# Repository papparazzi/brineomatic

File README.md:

# Brineomatic Rev D-12V: a lower-cost 12 V remix of Brineomatic Rev-C1

This fork of [hoeken/brineomatic](https://github.com/hoeken/brineomatic) holds **Rev D-12V**, a remix of the Brineomatic **Rev-C1** watermaker controller for boats with a **12 V** supply. It aims to do everything Rev-C1 does at 12 V and to cost much less when JLCPCB assembles it. Brineomatic itself, its firmware and its documentation are hoeken's work: see [brineomatic.com](https://brineomatic.com).

> [!WARNING]
> **Status on 14 Nov 2026: design proposal. No board has been built or bench-tested.**
>
> This is not upstream's Rev D: upstream is designing its own 24 V Rev D on `main`.
>
> The latest design is on branch [`rev-d-12v-c57-100uf`][branch] (step 27). Read [Before you order](#before-you-order) first.

![Rev D-12V, top side (KiCad render, unchanged since step 26)][render]

## Contents

- [At a glance](#at-a-glance)
- [Why Rev-C1 is expensive to assemble](#why-rev-c1-is-expensive-to-assemble)
- [Cost comparison](#cost-comparison)
- [Every change, and why](#every-change-and-why)
- [Independent review](#independent-review)
- [Before you order](#before-you-order)
- [Branches and documents](#branches-and-documents)
- [Credits and license](#credits-and-license)

## At a glance

| | Rev-C1 (hoeken) | Rev D-12V (this fork) |
|---|---|---|
| Supply | 12-30 V DC | **12 V only** (9-15 V) |
| Controller | ESP32-S3-WROOM-1 module soldered on, USB-C on the board | ESP32-S3-DevKitC-1-N16R8 v1.1 dev board in two sockets, USB on the dev board |
| Input protection | TPS26630 eFuse with an N-channel reverse-polarity MOSFET | two P-channel reverse-polarity MOSFETs, then a TPS16630 eFuse (step 25) |
| Connectors | JST-PH, a 5.08 mm terminal, two 2x3 pin headers | one family: 3.5 mm pluggable screw terminals |
| Board | 106 x 63.5 mm, 4 layers | 160 x 90 mm, 4 layers |
| JLCPCB assembly | Standard PCBA (three parts are "Standard only") | Economic PCBA, top side only |
| BOM lines | 80 | 59 |
| Line fees | US$1.38 on each of 80 lines: US$110.05 | US$3.09 on each of 15 charged Extended lines: US$46.35 |
| 5 assembled boards | about US$376, US$75 each | about US$223 with the dev boards, US$45 each |
| Firmware | Rev C firmware | the same GPIO numbers, so the Rev C firmware should run unchanged (not tested) |
| Field record | 433 running hours reported by its author | none: untested |

The cost comes down in four moves:

1. **A plug-in ESP32 dev board** instead of the soldered module, USB-C and their support parts. This removes two "Standard only" parts and 8 charged lines.
2. **12 V only.** 16 V TVS diodes and 30 V MOSFETs are available as parts that JLCPCB loads free.
3. **Fee-free parts everywhere else.** 15 charged Extended lines are left. Rev-C1's BOM had 42 in an Economic trial quote.
4. **Economic PCBA.** Setup and stencil cost US$9.79 instead of US$34.02, and Basic parts carry no line fee.

What it costs in return: a bigger board, no 24 V, no USB socket on the board, a new case, and no field record yet.

## Why Rev-C1 is expensive to assemble

JLCPCB offers two assembly services:

| | Standard PCBA | Economic PCBA |
|---|---|---|
| Limits | none that matter here | top side only, 2 or 5 boards |
| Setup + stencil (5 boards) | US$25.75 + US$8.27 | US$8.24 + US$1.55 |
| Line fee | about US$1.38 for **every** BOM line, Basic or not | US$3.09 per charged Extended line; Basic and promotional parts are free |
| Parts | all | not the parts marked "Standard only" |

Rev-C1 cannot use Economic PCBA as designed. Three of its parts are "Standard only":

- the ESP32-S3-WROOM-1 module (U5);
- the 220 uF electrolytic capacitors C21 and C23 (LCSC C2977551);
- the WS2812B status LED D40, which also has to be baked before assembly.

With those three left off, an Economic trial quote (12 Nov 2026) still charged 42 Extended lines (US$129.78) and came to US$296.65. The module, the capacitors and the LED would then still have to be bought and soldered by hand.

So the remix has two goals: no "Standard only" parts, and as few charged Extended lines as possible. Running at 12 V only and plugging in the controller are the two design decisions that make both possible.

## Cost comparison

Real JLCPCB quotes for five assembled boards, read on the quote pages. Nothing was ordered, and prices change daily.

| USD, 5 boards | Rev-C1, Standard PCBA, 12 Nov 2026 | Rev D-12V, Economic PCBA, 13 Nov 2026 (step 21) |
|---|---:|---:|
| Bare PCB, 4 layers (engineering fee 25.00 in both) | 52.40 (106 x 63.5 mm, blue, ENIG) | 33.90 (160 x 90 mm, green, HASL) |
| Setup and stencil | 34.02 | 9.79 |
| Components | 144.16 (80 lines) | 69.89 (57 lines) |
| Line fees | 110.05 (feeder loading, 80 lines) | 43.26 (14 charged Extended lines) |
| SMT, hand soldering, manual assembly, X-ray, packaging | 23.91 | 15.70 |
| **Quote total** | **364.54** | **172.54** |
| Billed after JLCPCB's review | about 11.25 (baking 7.94, depaneling 3.31) | - |
| Added since the quote, not re-quoted | - | about 17.04 (step-25 eFuse: 5 x 2.79 plus its Extended line, 3.09) |
| Bought separately | - | about 33 (five ESP32-S3-DevKitC-1-N16R8 v1.1, October estimate) |
| **Estimated total** | **about 376, or 75 per board** | **about 223, or 45 per board** |

Both totals leave out shipping, the fuse insert and the cable plugs.

- **Colour and finish.** Part of the PCB difference comes from Rev-C1's blue solder mask and ENIG finish. In green with leaded HASL, Rev-C1 quoted US$341.34 at Standard. Rev D-12V is still about 37 % cheaper than that.
- **eFuse supply.** The Rev-C1 quote already uses a second-source TPS26630 (US$5.79) because TI's part was out of stock. With TI parts, the October quote was US$434.45. On 13 Nov 2026 TI's TPS26630 cost US$11.89 with 2 in stock. The TPS16630 used in Rev D-12V cost US$2.79 with 2,760 in stock.
- **Rev D-12V quote history** (5 boards, Economic): US$187.73 (30 Oct, first quote), 175.20 (sockets added to the BOM, fee-bearing parts swapped), 177.52 (screw terminals), 178.51 (servo and TDS terminals), 172.54 (13 Nov, 160 x 90 mm board). Details in the [working log][plan] and the [parts check][partscheck].

## Every change, and why

Rev-C1 has 302 parts and Rev D-12V has 272. 180 parts are identical; 130 are changed, added or removed. Every one of them has an ID in the [change register][register], with datasheet figures, calculations and open items. The [audit][audit] is generated by a script that fails if any part difference has no register ID; it finds none. The sections below summarise each change and what it does to cost. Register IDs are given in brackets.

### 1. Controller: a plug-in dev board instead of a soldered module (A2)

**Removed:** the ESP32-S3-WROOM-1 module (U5), the USB-C socket (J19), the boot and reset buttons (SW1, SW2), USB ESD protection (U6), the WS2812B status LED (D40), the level shifter (U8), the 3.3 V regulator (U7), and their support parts (C37-C43, R43-R53, D36-D38, FB1, J20, J24, TP27-TP29).

**Added:** two 1x22 sockets for an Espressif **ESP32-S3-DevKitC-1-N16R8, board v1.1**, and a diode (D57, SS34) in the dev board's 5 V feed.

**Why it saves money:**
- The module and the status LED are "Standard only" at JLCPCB. Without them the board can use Economic PCBA.
- 8 fewer charged lines.
- The dev board costs about US$6.60 and plugs in, so a failed or outdated controller can be swapped in a minute without soldering.

**Trade-offs:**
- Only board v1.1 works as is: its RGB LED is on GPIO38. On v1.0 and on some clones the LED is on GPIO48, which is RS-485 transmit on this board.
- The dev board's regulator now feeds every 3.3 V load: about 65 mA for the board's own parts, plus the ESP32.
- USB is on the dev board. D57 stops USB power from back-feeding the board's 5 V rail.
- All 22 pin assignments of the Rev C firmware (v2.9.0) match the sockets, so the firmware should run unchanged. This was checked on paper, not on hardware ([pin audit][pinaudit]).

### 2. 12 V only (A4, B1, B4)

| Part | Rev-C1 | Rev D-12V | Why |
|---|---|---|---|
| Main supply rail | +24V, 12-30 V input | +12V, 9-15 V input; "12V ONLY" printed twice on the board | Most boats, including this build, have a 12 V house bus. |
| TVS diodes D15, D19, D27, D30, D33, D48 | SMBJ30CA | SMBJ16CA, bidirectional | Loads free. The 16 V standoff is above a 14.8 V charge voltage, and the clamp is about 26 V instead of about 48 V, so the stepper driver, the buck converter and the MOSFETs see less in a surge. |
| N-channel MOSFETs Q1, Q2, Q4-Q7 | Si2318, 40 V | AO3400A, 30 V | Basic part; turns on better from a 3.3 V gate. 30 V is enough once the rail is 12 V and clamped at about 26 V. |

**Trade-off:** a 24 V supply destroys the input TVS diode, the MOSFETs and the fuse.

### 3. Input protection: two MOSFETs, then a smaller eFuse (A1, K1)

| | Rev-C1 | Rev D-12V, steps 1-24 | Rev D-12V, step 25 (now) |
|---|---|---|---|
| Parts | TPS26630 eFuse (QFN-24, Extended), CSD19537 N-channel MOSFET, BSS138, R21, R72-R77, C15, test points TP50-TP52 | two AO3401A P-channel MOSFETs (fee-free), 10 kOhm gate pull-down, BZT52C10 zener gate clamp | the two MOSFETs, then a TI **TPS16630** eFuse (HTSSOP-20) with six resistors and two capacitors |
| Reverse polarity | blocked | blocked | blocked |
| Current limit | 4 A | none: fuse only | 3.8 A; a short is cut off within about 1 us |
| Overvoltage cut-off | yes | none: TVS diodes only | above 16.9 V |
| Soft start | yes | no | 25 ms |
| Undervoltage lockout | yes | no | no (owner's decision) |
| Reverse-current blocking | yes | no | no |
| eFuse price, stock (13 Nov 2026) | TPS26630: US$11.89, 2 in stock | - | TPS16630: US$2.79, 2,760 in stock |

Steps 1-24 dropped the eFuse to save its charged line and its many support parts. The independent review then pointed out that nothing limited a short any more (finding M2), so step 25 put a smaller eFuse back after the MOSFETs. It loads at Economic and adds about US$17 per five boards, its line fee included. Detail: [EFUSE.md][efuse].

### 4. Semiconductor swaps to fee-free parts (B2, B3, B5, B6, C4)

| Parts | Rev-C1 | Rev D-12V | Why it saves money | Effect |
|---|---|---|---|---|
| D1, D2, D4, D6, D9, D10, D24, D35, D42, D44, D50-D55 | SMF30CA, SMAJ5.0A, PSM712, BAT54S, BAV199 | the same parts from fee-free sources; BAV99 instead of BAV199 | no line fee | BAV99 leaks more; at most about 0.3 mV on the ADC inputs at 25 C |
| D14, D26, D29, D32, D47, D49 | SS54, 5 A | SS34, 3 A, 40 V | Basic part | outputs are limited to 3 A anyway |
| D13, D21, D22, D25, D28, D31, D39, D46 | green LEDs | red LEDs | red 0603 is Basic, green is not | status LEDs are red |
| D18 | B5819W | 1N4148W | Basic; an SS34 would collide with the buzzer | 0.7 V clamp instead of about 0.3 V, harmless |
| U10 | MAX3485 | SP3485EN | Basic part | pin-compatible 3.3 V RS-485 transceiver |

### 5. Passive parts (C1-C4)

| Parts | Rev-C1 | Rev D-12V | Why | Effect |
|---|---|---|---|---|
| C3, C24 (flow-meter filter), C18 (buck compensation) | 2.7 nF | 2.2 nF | Basic value | filter corner and compensation zero 20 % higher |
| C52, C53, C55, C56 | 47 pF part in the BOM (470 pF intended, [upstream issue 4](https://github.com/hoeken/brineomatic/issues/4)) | 470 pF, 50 V | fixes the BOM mistake with a Basic part | - |
| C11-C14, C22, C46, C49 | 10 uF, 1210 | 10 uF, 50 V, 1206 | Basic part | - |
| C21, C23 | 220 uF, 16 V, "Standard only" | 220 uF, 16 V, C3342 | loads at Economic | 2.3 mm taller; still a charged line |
| R26 | 11.8 kOhm | 12 kOhm | Basic value | 5 V rail at 4.93 V instead of 5.00 V |
| R27 | 100 kOhm | 47 kOhm | the power LED gets the same current at 12 V as Rev-C1's at 24 V | - |
| R23, R25 | 82 kOhm, 62 kOhm | same values, other LCSC parts | R25's original part was short of stock | - |

C57, the 100 uF bulk capacitor of the stepper driver's supply, was 47 uF from October to step 26 to avoid a line fee. JLCPCB's line-by-line test on 1 Nov 2026 showed that line is charged anyway, and none of the 1,146 100 uF SMD electrolytics at JLCPCB is fee-free, so step 27 put Rev-C1's part back. This also closes the review's minor finding m6: the TMC2209 datasheet recommends at least 100 uF near the driver.

### 6. Connectors: one family of 3.5 mm pluggable screw terminals (D1, D2)

| Connector | Rev-C1 | Rev D-12V |
|---|---|---|
| Power in, J10 | 5.08 mm terminal | 3.5 mm 2-pin terminal |
| Sensors and stepper: J3, J18 (2-pin), J4, J5, J11, J22 (3-pin), J21 (4-pin) | JST-PH, crimped | 3.5 mm 2-, 3- and 4-pin terminals |
| RS-485, J23 | 3.5 mm 3-pin terminal | the same part, moved to the bottom edge |
| Servos and TDS sensors, J1 and J6 | two 2x3 pin headers | four 3-pin terminals on the east edge: J6 and J29 for servos 1 and 2, J1 and J28 for the brine and product TDS sensors |

**Why:** one connector family, field wiring without crimp tools, 8 A per pin instead of 2 A for JST-PH, and the 2x3 headers could not be placed correctly in JLCPCB's viewer.

**Cost effect:** connectors load free at Economic either way. The terminals cost about US$2.32 more per five boards than JST-PH (31 Oct quotes). JLCPCB does not assemble the cable plugs: buy them separately (LCSC C5188249, C5188250, C5188251, about US$0.13 each).

**Trade-off:** the TDS signals now run about 94 and 101 mm instead of about 15 mm. The [analysis][tds] finds noise is not a concern, and their ESD diodes D8 and D41 were moved next to the terminals (step 17).

### 7. Board outline, mounting holes and case (A3, steps 20, 21, 23)

- The outline grew from 106 x 63.5 mm to **160 x 90 mm**: a strip on the west side for the dev board, and strips along the top and east edges for the screw terminals.
- The mounting holes moved to the four corners (152 x 82 mm pattern), and the power plug lines up with the bottom row of plugs.
- **Cost:** the bare boards cost US$8.90 instead of US$4.90 per five; the US$25 engineering fee is the same.
- **The Rev C case does not fit.** A new case is being designed in [`rev-d-12v/case`][case]: a base, and a cover with plug notches and a window for a 2.42" OLED. The firmware has no display support yet.

### 8. Silkscreen and usability (I1, steps 19 and 21)

- Every dev-board pin is labelled, and 15 breakout pads sit beside the unused dev-board pins.
- Every plug has its name and a legend for each pin (for example S, 5V, 12V, GND) in white boxes.
- The dev-board type is printed inside the socket outline, with a credits block for the remix and the original design, and "12V ONLY" warnings.
- **Cost:** none; the silkscreen is free.

### 9. Layout fixes and checks (steps 22, 24, 25 and 26)

- Step 22: no copper fill under the Wi-Fi antenna end of the dev board.
- Step 24: the path from the fuse to the MOSFETs is rebuilt with wide copper (2.3 and 3.1 mOhm instead of 34 and 45 mOhm), and the placement file now carries JLCPCB's rotation corrections, as Rev-C1's did ([review fixes][fixes]).
- Step 25: the eFuse area (section 3).
- Step 26: the servo 5 V supply moves from 0.25 mm inner-layer tracks to 1.8-4.0 mm top-layer copper, 13 mOhm from F2 to each servo terminal instead of 161-230 mOhm ([SERVO_POWER.md][servo]). No part moved.
- Step 27: C57 back to Rev-C1's 100 uF (section 5; review finding m6). Copper and silkscreen do not change.
- After every step: KiCad DRC with schematic parity, ERC, an independent copper trace from every plug pin, and the audit against Rev-C1.

### 10. Manufacturing files and scripts

- [`rev-d-12v/mfg`][mfg]: BOM and placement file for JLCPCB Economic PCBA, with and without cable plugs, and the gerbers of the latest step.
- [`rev-d-12v/tools`][tools]: every schematic and PCB change was made by a script (KiCad 10 Python), so each step can be re-run and checked.
  - `make_jlc.py` writes the BOM and placement file using JLCPCB's centre and rotation rules.
  - `audit_changes.py` fails if any difference to Rev-C1 has no register entry.
  - `trace_connectors.py` follows the copper from every plug pin without relying on KiCad's DRC.

### 11. Kept from Rev-C1 on purpose (E)

Every ESP32 net name and GPIO number; the TMC2209 stepper driver; the RT7272 5 V buck converter and its inductor; the MAX40200 ideal diode; the ADS1115 ADC; the PESD3V3L1BA and PSD12C ESD parts; the 0.1 % 100 Ohm shunts of the 4-20 mA inputs; the stepper sense resistors; the JST-SH I2C header; the F2 polyfuse; and the 4-20 mA sensor circuit.

These include the 14 charged lines for which no fee-free part with the same function was found: two electrolytic-capacitor lines, PESD3V3L1BA, PSD12C, the mSMD260 polyfuse, the ferrites, the JST-SH header, the 6.8 uH inductor, the 0.1 % and 0.11 Ohm resistors, ADS1115, RT7272, MAX40200 and TMC2209. The TPS16630 eFuse is the 15th since step 25.

### 12. What this remix gives up

- 24 V operation.
- The USB-C socket and the 3.3 V regulator on the board (the dev board has both).
- Undervoltage lockout and reverse-current blocking. Current limit, overvoltage cut-off and soft start are back since step 25.
- Green status LEDs (they are red).
- The fit in the Rev C case, and the smaller board.
- Rev-C1's field record: none of these changes has been tested yet.

## Independent review

An independent design review of step 22 (13 Nov 2026, by an AI model in a separate session; the brief is in [INDEPENDENT_REVIEW_BRIEF.md][brief]) found two blockers, four major findings and eleven minor ones. All six blockers and majors are now fixed or closed by the owner's decision; of the minor findings, m6 is fixed and the rest are open.

| Finding | Status |
|---|---|
| B1: the path from the fuse to the MOSFETs was signal-width copper | fixed in step 24 |
| B2: the placement file lacked JLCPCB's rotation corrections | fixed in step 24 |
| M1: the servo 5 V supply ran on 0.25 mm inner-layer tracks (161-230 mOhm) | fixed in step 26: 1.8-4.0 mm top-layer copper, 13 mOhm |
| M2: nothing limited a short after the eFuse was removed | fixed in step 25 (TPS16630) |
| M3: no undervoltage lockout | accepted by the owner |
| M4: 4-20 mA sensor headroom at low battery | dropped: the circuit is the same as Rev-C1's, and the battery is assumed to stay at 12 V or above |
| m6: C57 halved to 47 uF, against the TMC2209 datasheet's 100 uF minimum | fixed in step 27: 100 uF again, as Rev-C1 |
| Other minor findings (m1-m5, m7-m11), note N1 | open |

Detail: [REVIEW_FIXES.md][fixes], [EFUSE.md][efuse], [SERVO_POWER.md][servo] and section M of the [change register][register].

## Before you order

1. **Nothing has been built.** Follow the [bring-up test plan][bringup], from part orientation to the eFuse and servo-supply tests.
2. **No human has reviewed the layout yet.** It was routed with Freerouting and scripts.
3. **At JLCPCB:** choose Economic PCBA, 2 or 5 boards, top side. Upload the gerbers, `BOM-rev_d.csv` and `CPL-rev_d.csv` from [`rev-d-12v/mfg`][mfg].
   - Tick the dev-board socket line by hand; it comes up unselected.
   - In the placement preview, check every MOSFET, diode, LED, IC and electrolytic capacitor against its pin-1 or cathode mark, U3 and D49 above all.
   - Tick the option to confirm the placement before production.
4. **Buy separately:**
   - five ESP32-S3-DevKitC-1-N16R8, board v1.1 (not v1.0, not clones with the LED on GPIO48);
   - the cable plugs;
   - a 5 x 20 mm 3.15 A time-lag fuse.
5. **12 V only.** Never connect 24 V.

## Branches and documents

| Branch | Steps | Content |
|---|---|---|
| `main` | - | upstream's `main` (hoeken's work after Rev-C1, including his own Rev D) plus this page |
| [`rev-d-12v`][b-17] | 1-17 | the remix up to the TDS ESD fix (31 Oct 2026) |
| [`rev-d-12v-stepper-socket`][b-18] | 18 | an alternative with a plug-in TMC2209 module, branched off `rev-d-12v`; not adopted |
| [`rev-d-12v-labels`][b-23] | 19-23 | labels, breakout pads, 160 x 90 mm board, corner holes, antenna keep-out, power plug alignment, case design |
| [`rev-d-12v-review-fixes`][b-24] | 24 | the review's two blockers fixed |
| [`rev-d-12v-efuse`][b-25] | 25 | the TPS16630 eFuse |
| [`rev-d-12v-servo-power`][b-26] | 26 | the servo 5 V supply on wide copper |
| [`rev-d-12v-c57-100uf`][branch] | 27 | C57 back to Rev-C1's 100 uF: **latest design** |

Each step branch builds on the one above it, so the latest branch contains every step. Rev D-12V starts from the **Rev-C1 tag** (`dd1f660`), not from upstream's `main`, which has moved on since (18 commits as of 14 Nov 2026). In the KiCad project in `brineomatic/`, `git diff Rev-C1` shows every change.

Documents (all in `rev-d-12v/docs/` on the latest branch):

| Document | Content |
|---|---|
| [GOALS.md][goals] | goals, what is given up, relationship to upstream |
| [CHANGE_REGISTER.md][register] | every change with datasheet figures, calculations and open items |
| [CHANGE_AUDIT.md][audit] | the complete generated part diff against Rev-C1 |
| [REDESIGN_PLAN.md][plan] | the working log, with every JLCPCB quote |
| [VETTING.md][vetting] | power-stage calculations and fee-free part searches |
| [PARTS_CHECK_2026-11-13.md][partscheck] | stock check and the 13 Nov 2026 quote |
| [LABELS_BREAKOUT.md][labels] | steps 19-23: labels, breakout pads, outline, holes |
| [DEVBOARD_PIN_AUDIT.md][pinaudit] | dev-board pins against the firmware |
| [TDS_SIGNAL_ANALYSIS.md][tds] | the long TDS signal routes |
| [REVIEW_FIXES.md][fixes] | step 24 and the review's findings |
| [EFUSE.md][efuse] | step 25 |
| [SERVO_POWER.md][servo] | step 26 |
| [BRINGUP_TEST_PLAN.md][bringup] | bench tests for the first boards |
| [INDEPENDENT_REVIEW_BRIEF.md][brief] | the brief given to the reviewer |

## Credits and license

- **Brineomatic** is designed by [hoeken](https://github.com/hoeken/brineomatic) and is part of the Yarrboard ecosystem. Documentation: [brineomatic.com](https://brineomatic.com). Upstream's own README for this repository points there for all documentation.
- **Rev D-12V** is a remix of the Rev-C1 tag by [papparazzi](https://github.com/papparazzi). It is not an official Brineomatic revision.
- **License:** the same terms as upstream. The repository's [LICENSE](LICENSE) file is the GNU LGPL v2.1. Upstream's Rev-C1 README names GPLv3 for the firmware and an Open Hardware License for the hardware.

[branch]: https://github.com/papparazzi/brineomatic/tree/rev-d-12v-c57-100uf
[render]: https://raw.githubusercontent.com/papparazzi/brineomatic/rev-d-12v-c57-100uf/rev-d-12v/docs/rev_d_pcb_step26_top.png
[b-25]: https://github.com/papparazzi/brineomatic/tree/rev-d-12v-efuse
[b-26]: https://github.com/papparazzi/brineomatic/tree/rev-d-12v-servo-power
[servo]: https://github.com/papparazzi/brineomatic/blob/rev-d-12v-c57-100uf/rev-d-12v/docs/SERVO_POWER.md
[b-17]: https://github.com/papparazzi/brineomatic/tree/rev-d-12v
[b-18]: https://github.com/papparazzi/brineomatic/tree/rev-d-12v-stepper-socket
[b-23]: https://github.com/papparazzi/brineomatic/tree/rev-d-12v-labels
[b-24]: https://github.com/papparazzi/brineomatic/tree/rev-d-12v-review-fixes
[mfg]: https://github.com/papparazzi/brineomatic/tree/rev-d-12v-c57-100uf/rev-d-12v/mfg
[tools]: https://github.com/papparazzi/brineomatic/tree/rev-d-12v-c57-100uf/rev-d-12v/tools
[case]: https://github.com/papparazzi/brineomatic/tree/rev-d-12v-c57-100uf/rev-d-12v/case
[goals]: https://github.com/papparazzi/brineomatic/blob/rev-d-12v-c57-100uf/rev-d-12v/docs/GOALS.md
[register]: https://github.com/papparazzi/brineomatic/blob/rev-d-12v-c57-100uf/rev-d-12v/docs/CHANGE_REGISTER.md
[audit]: https://github.com/papparazzi/brineomatic/blob/rev-d-12v-c57-100uf/rev-d-12v/docs/CHANGE_AUDIT.md
[plan]: https://github.com/papparazzi/brineomatic/blob/rev-d-12v-c57-100uf/rev-d-12v/docs/REDESIGN_PLAN.md
[vetting]: https://github.com/papparazzi/brineomatic/blob/rev-d-12v-c57-100uf/rev-d-12v/docs/VETTING.md
[partscheck]: https://github.com/papparazzi/brineomatic/blob/rev-d-12v-c57-100uf/rev-d-12v/docs/PARTS_CHECK_2026-11-13.md
[labels]: https://github.com/papparazzi/brineomatic/blob/rev-d-12v-c57-100uf/rev-d-12v/docs/LABELS_BREAKOUT.md
[pinaudit]: https://github.com/papparazzi/brineomatic/blob/rev-d-12v-c57-100uf/rev-d-12v/docs/DEVBOARD_PIN_AUDIT.md
[tds]: https://github.com/papparazzi/brineomatic/blob/rev-d-12v-c57-100uf/rev-d-12v/docs/TDS_SIGNAL_ANALYSIS.md
[fixes]: https://github.com/papparazzi/brineomatic/blob/rev-d-12v-c57-100uf/rev-d-12v/docs/REVIEW_FIXES.md
[efuse]: https://github.com/papparazzi/brineomatic/blob/rev-d-12v-c57-100uf/rev-d-12v/docs/EFUSE.md
[bringup]: https://github.com/papparazzi/brineomatic/blob/rev-d-12v-c57-100uf/rev-d-12v/docs/BRINGUP_TEST_PLAN.md
[brief]: https://github.com/papparazzi/brineomatic/blob/rev-d-12v-c57-100uf/rev-d-12v/docs/INDEPENDENT_REVIEW_BRIEF.md

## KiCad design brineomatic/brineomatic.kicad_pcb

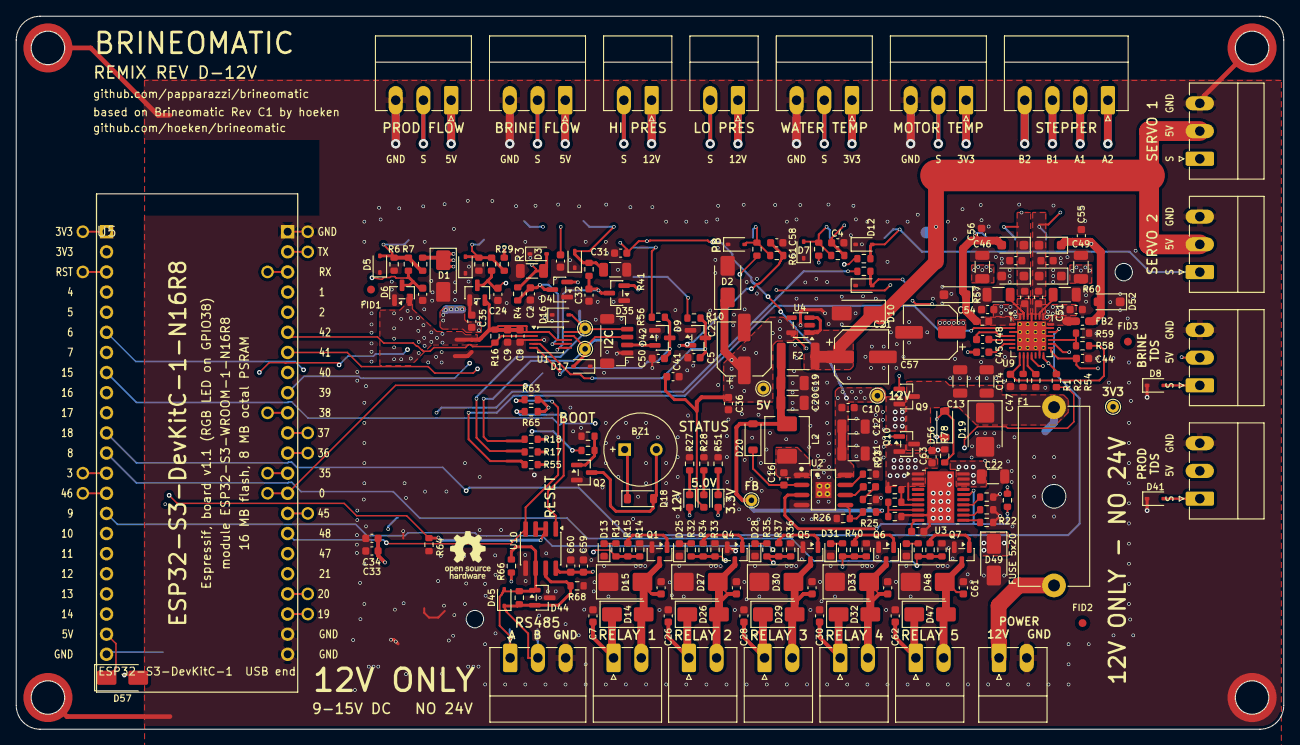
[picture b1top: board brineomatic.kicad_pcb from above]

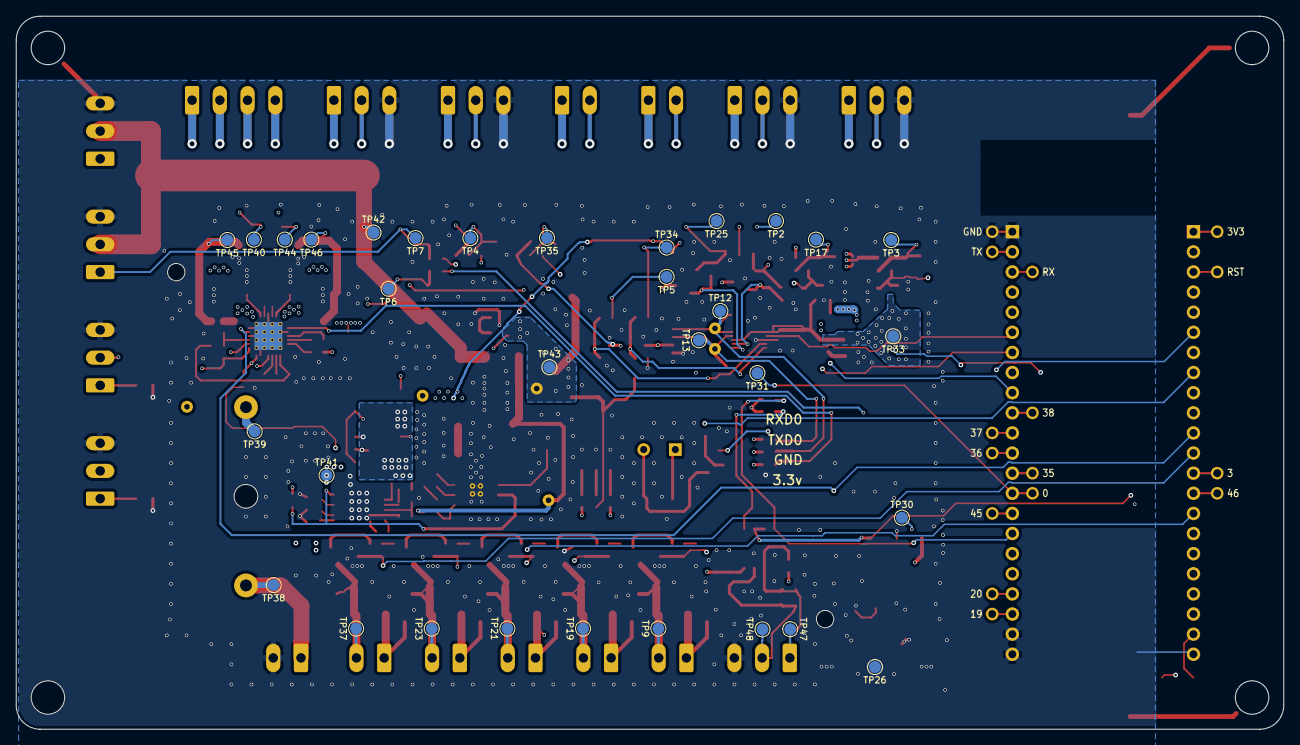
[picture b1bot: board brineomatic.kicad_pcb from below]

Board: 4 copper layers, 160.0 x 90.0 mm, 266 parts (32 on the bottom side), 103 nets.

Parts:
BZ1: Buzzer; MagneticBuzzer_QMB-09B-03
C1, C4, C6, C7, C25, C26, C27, C28, C29, C30, C31, C35, C58, C61, C62, C63: 1uF; C_0603_1608Metric
C2, C5, C8, C10, C15, C16, C32, C34, C36, C41, C44, C45, C50, C51, C54, C60: 100nF; C_0603_1608Metric
C3, C18, C24: 2.2nF; C_0603_1608Metric
C9, C59: 10uF; C_0603_1608Metric
C11, C12, C13, C14, C22, C46, C49: 10uF; C_1206_3216Metric
C19, C20: 22uF; C_1206_3216Metric
C21, C23: 220uF / 16v; CP_Elec_6.3x7.7
C33: 22uF; C_0603_1608Metric
C47: 4.7uF; C_0603_1608Metric
C48: 22nF / 50v; C_0603_1608Metric
C52, C53, C55, C56: 470pF / 50V; C_0603_1608Metric
C57: 100uF / 35v; CP_Elec_6.3x7.7
D1, D2, D10: SMAJ5.0A; D_SMA
D3, D5, D7, D8, D11, D12, D16, D17, D23, D34, D41, D43: PESD3V3L1BA; D_SOD-323
D4, D9, D35, D42: BAV99; SOT-23
D6, D24: BAT54S; SOT-23
D13, D21, D22, D25, D28, D31, D39, D46: RED; LED_0603_1608Metric
D14, D26, D29, D32, D47, D49, D57: SS34; D_SMA
D15, D19, D27, D30, D33, D48: SMBJ16CA; D_SMB
D18, D20: 1N4148W; D_SOD-123
D44: PSM712; SOT-23
D45: PSD12C; D_SOD-323
D50, D51, D52, D53, D54, D55: SMF30CA; D_SOD-123F
D56: BZT52C10; D_SOD-123
F1: 5x20mm; Fuseholder_Cylinder-5x20mm_LittelFuse_646
F2: mSMD260; Fuse_1812_4532Metric
FB2, FB3, FB4, FB5: 50ohm @ 100mhz; L_0603_1608Metric
FID1, FID2, FID3: Fiducial; Fiducial_1mm_Mask2mm
H1, H2, H3, H4: Standoff; SMTSO30XXX
H5, H6: Alignment Hole; MountingHole_2.2mm_M2
J1, J4, J5, J6, J11, J22, J23, J28, J29: 3.5MM; PhoenixContact_MC_1,5_3-G-3.5_1x03_P3.50mm_Horizontal
J2: Conn_01x04_MountingPin; JST_SH_BM04B-SRSS-TB_1x04-1MP_P1.00mm_Vertical
J3, J7, J10, J12, J14, J16, J18, J25: 3.5MM; PhoenixContact_MC_1,5_2-G-3.5_1x02_P3.50mm_Horizontal
J21: 3.5MM; PhoenixContact_MC_1,5_4-G-3.5_1x04_P3.50mm_Horizontal
L2: 6.8uH; L_Chilisin_BMRA00050530
Q1, Q2, Q4, Q5, Q6, Q7: AO3400A; SOT-23
Q9, Q10: AO3401A; SOT-23
R1, R2, R4, R10, R14, R16, R20, R28, R33, R36, R39, R42, R56, R59, R63, R64, R65, R70, R78: 10k; R_0603_1608Metric
R3, R41: 100R 0.1%; R_1206_3216Metric
R5, R29: 1.2K; R_0603_1608Metric
R6, R17, R18, R30, R74: 2.2k; R_0603_1608Metric
R7, R8, R31, R61, R73, R76: 4.7K; R_0603_1608Metric
R9, R11, R12, R62: 100R; R_0603_1608Metric
R13, R32, R35, R38, R54, R69: 1k; R_0603_1608Metric
R15, R19, R34, R37, R40, R71: 220R; R_0603_1608Metric
R22, R24, R72: 24k; R_0603_1608Metric
R23: 82k 1%; R_0603_1608Metric
R25: 62k 1%; R_0603_1608Metric
R26: 12k; R_0603_1608Metric
R27: 47k; R_0603_1608Metric
R51: 5.1k; R_0603_1608Metric
R55, R58, R66, R68, R77: 20k; R_0603_1608Metric
R57, R60: 0.11R 1%; R_1206_3216Metric
R67: 120R; R_0603_1608Metric
R75: 0R; R_0603_1608Metric
SYM1: Logo_Open_Hardware_Small; OSHW-Logo_5.7x6mm_SilkScreen
TP2, TP3, TP4, TP5, TP6, TP7, TP9, TP12, TP13, TP17, TP19, TP21, TP23, TP25, TP26, TP30, TP31, TP33, TP34, TP35, TP37, TP38, TP39, TP40, TP41, TP42, TP43, TP44, TP45, TP46, TP47, TP48: TestPoint; TestPoint_Pad_D1.5mm
TP10, TP11, TP14, TP15, TP16, TP32: TestPoint_THTPad_D1.5mm_Drill0.7mm
U1: ADS1115IDGSR; TSSOP-10_3x3mm_P0.5mm
U2: RT7272BGSP; SOIC-8_L5.0-W4.0-P1.27-LS6.0-BL-EP2.0
U3: TPS16630PWPR; HTSSOP-20-1EP_4.4x6.5mm_P0.65mm_EP3.4x6.5mm_Mask2.96x2.96mm
U4: MAX40200AUK; SOT-23-5
U5: ESP32-S3-DevKitC-1; ESP32-S3-DevKitC-1_Sockets
U9: TMC2209-LA; VQFN-28-1EP_5x5mm_P0.5mm_EP3.7x3.7mm_ThermalVias
U10: SP3485EN; SOIC-8_3.9x4.9mm_P1.27mm

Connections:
5V_HIGH_POWER: C21.1, D10.1 (A1), F2.1, J6.2, J29.2, TP42.1, U4.1 (VDD), U4.3 (EN)
+3.3V: BZ1.1 (+), C4.1, C8.1, C9.1, C33.1, C34.1, C44.1, C58.1, C59.1, C60.1, D4.2 (K), D6.2 (K), D9.2 (K), D18.1 (K), D24.2 (K), D35.2 (K), D39.2 (A), D42.2 (K), J2.2, J5.1, J22.1, R8.2, R16.2, R17.2, R18.2, R55.1, R61.2, R63.2, R65.2, R66.2, TP32.1, TP33.1, U1.1 (ADDR), U1.8 (VDD), U5.2, U9.15 (VCC_IO), U10.8 (VCC)
+5V: C23.1, C35.1, C36.1, C41.1, D1.1 (A1), D2.1 (A1), D22.2 (A), D57.2 (A), J1.2, J4.1, J11.1, J28.2, R5.2, R29.2, TP16.1, TP43.1, U4.5 (OUT)
+12V: C1.2, C7.2, C10.1, C11.1, C12.1, C22.2, C26.2, C28.2, C30.2, C31.2, C45.2, C46.1, C49.1, C51.2, C54.2, C57.1, C62.2, D14.1 (K), D21.2 (A), D26.1 (K), D29.1 (K), D32.1 (K), D47.1 (K), D49.1 (K), J3.1, J7.1, J12.1, J14.1, J16.1, J18.1, J25.1, R22.1, TP15.1, TP41.1, U2.8 (VIN), U3.18, U3.19, U3.20, U9.22 (VS), U9.28 (VS)
/ADC/ADC0: C5.1, D9.3 (COM), R10.2, U1.4 (AIN0)
/ADC/ADC1: C50.1, D42.3 (COM), R56.2, U1.5 (AIN1)
/ADC/ADC2: C32.1, D35.3 (COM), R42.2, U1.6 (AIN2)
/ADC/ADC3: C2.1, D4.3 (COM), R4.2, U1.7 (AIN3)
/ESP32-S3/EN: TP30.1, U5.3
/ESP32-S3/ESP_5V: D57.1 (K), U5.42
/ESP32-S3/GPIO0_BOOT: TP31.1, U5.27
/Power Supply/EF_OVP: R73.2, R74.1, U3.8
/Power Supply/EF_UVLO: R72.2, R73.1, U3.7
/Power Supply/PFET_G: D56.2 (A), Q9.1 (G), Q10.1 (G), R78.1
/Power Supply/PFET_OUT: C63.1, D56.1 (K), Q9.2 (S), Q10.2 (S), R72.1, U3.1, U3.2, U3.3, U3.6
/Power Supply/PRE_24: C13.2, C14.2, D19.1 (A1), F1.2, Q9.3 (D), Q10.3 (D), TP39.1
/Power Supply/SW: C16.2, L2.1, U2.1 (SW)
/Stepper Driver/MS1: R1.1, U9.9 (MS1/AD0)
/Stepper Driver/MS2: R2.1, U9.10 (MS2/AD1)
/Stepper Driver/OA1: FB3.1, U9.24 (OA1)
/Stepper Driver/OA2: FB2.1, U9.21 (OA2)
/Stepper Driver/OB1: FB4.1, U9.26 (OB1)
/Stepper Driver/OB2: FB5.1, U9.1 (OB2)
ADC_ALERT: R16.1, U1.2 (ALERT/RDY), U5.35
BRINE_FLOWMETER: C24.1, D24.3 (COM), R31.2, U5.38
BRINE_TDS: D8.2 (A2), J1.1, R10.1, TP5.1
BUZZER: R19.2, U5.22
GND: C1.1, C2.2, C3.2, C4.2, C5.2, C6.1, C7.1, C8.2, C9.2, C10.2, C11.2, C12.2, C13.1, C14.1, C15.2, C19.2, C20.2, C21.2, C22.1, C23.2, C24.2, C25.1, C26.1, C27.1, C28.1, C29.1, C30.1, C31.1, C32.2, C33.2, C34.2, C35.2, C36.2, C41.2, C44.2, C46.2, C47.2, C49.2, C50.2, C51.1, C52.1, C53.2, C54.1, C55.1, C56.2, C57.2, C58.2, C59.2, C60.2, C61.1, C62.1, C63.2, D1.2 (A2), D2.2 (A2), D3.1 (A1), D4.1 (A), D5.1 (A1), D6.1 (A), D7.1 (A1), D8.1 (A1), D9.1 (A), D10.2 (A2), D11.1 (A1), D12.1 (A1), D13.1 (K), D15.1 (A1), D16.1 (A1), D17.1 (A1), D19.2 (A2), D23.1 (A1), D24.1 (A), D25.1 (K), D27.1 (A1), D28.1 (K), D30.1 (A1), D31.1 (K), D33.1 (A1), D34.1 (A1), D35.1 (A), D41.1 (A1), D42.1 (A), D43.1 (A1), D44.3 (common), D46.1 (K), D48.1 (A1), D49.2 (A), D52.1 (A1), D53.2 (A2), D54.1 (A1), D55.2 (A2), H1.1, H2.1, H3.1, H4.1, J1.3, J2.1, J2.MP (MountPin), J4.3, J5.3, J6.3, J10.2, J11.3, J22.3, J23.3, J28.3, J29.3, Q1.2 (S), Q2.2 (S), Q4.2 (S), Q5.2 (S), Q6.2 (S), Q7.2 (S), R1.2, R2.2, R3.1, R6.1, R14.1, R20.2, R23.2, R24.2, R26.2, R27.2, R28.2, R30.1, R33.1, R36.1, R39.1, R41.1, R51.2, R57.1, R59.1, R60.2, R64.1, R68.1, R70.1, R74.2, R75.2, R76.2, R77.2, R78.2, TP26.1, U1.3 (GND), U2.4 (GND), U3.9, U3.21, U4.2 (GND), U5.1, U5.40, U5.41, U9.3 (GND), U9.13 (CLK), U9.18 (GND), U9.20 (STDBY), U9.25 (NC), U9.29 (GND), U10.5 (GND)
MOTOR_TEMPERATURE: R9.1, U5.4
unnamed: BZ1.2 (-), D18.2 (A), Q2.3 (D)
unnamed: C18.1, R24.1
unnamed: D3.2 (A2), J3.2, R3.2, R4.1, TP2.1
unnamed: D5.2 (A2), J4.2, R5.1, R6.2, R7.1, TP3.1
unnamed: D7.2 (A2), J5.2, R8.1, R9.2, TP4.1
unnamed: D11.2 (A2), J6.1, R11.1, TP6.1
unnamed: D12.2 (A2), J29.1, R12.2, TP7.1
unnamed: D13.2 (A), R13.1
unnamed: C6.2, D14.2 (A), D15.2 (A2), J7.2, Q1.3 (D), TP9.1
unnamed: C19.1, C20.1, D20.2 (A), F2.2, L2.2, R25.1, TP14.1
unnamed: C16.1, D20.1 (K), U2.2 (BOOT)
unnamed: D21.1 (K), R27.1
unnamed: D22.1 (K), R28.1
unnamed: D23.2 (A2), J11.2, R29.1, R30.2, R31.1, TP17.1
unnamed: D25.2 (A), R32.1
unnamed: C25.2, D26.2 (A), D27.2 (A2), J12.2, Q4.3 (D), TP19.1
unnamed: D28.2 (A), R35.1
unnamed: C27.2, D29.2 (A), D30.2 (A2), J14.2, Q5.3 (D), TP21.1
unnamed: D31.2 (A), R38.1
unnamed: C29.2, D32.2 (A), D33.2 (A2), J16.2, Q6.3 (D), TP23.1
unnamed: D34.2 (A2), J18.2, R41.2, R42.1, TP25.1
unnamed: D39.1 (K), R51.1
unnamed: D43.2 (A2), J22.2, R61.1, R62.2, TP35.1
unnamed: D44.1 (A1), D45.2 (A2), J23.1, R66.1, R67.2, TP47.1, U10.6 (A)
unnamed: D44.2 (A2), D45.1 (A1), J23.2, R67.1, R68.2, TP48.1, U10.7 (B)
unnamed: D46.2 (A), R69.1
unnamed: C61.2, D47.2 (A), D48.2 (A2), J25.2, Q7.3 (D), TP37.1
unnamed: C55.2, D50.1 (A1), D52.2 (A2), FB2.2, J21.1, TP45.1
unnamed: C52.2, D50.2 (A2), D54.2 (A2), FB3.2, J21.2, TP40.1
unnamed: C53.1, D51.1 (A1), D55.1 (A1), FB4.2, J21.3, TP44.1
unnamed: C56.1, D51.2 (A2), D53.1 (A1), FB5.2, J21.4, TP46.1
unnamed: F1.1, J10.1, TP38.1
unnamed: Q1.1 (G), R15.2
unnamed: Q2.1 (G), R19.1, R20.1
unnamed: Q4.1 (G), R34.2
unnamed: Q5.1 (G), R37.2
unnamed: Q6.1 (G), R40.2
unnamed: Q7.1 (G), R71.2
unnamed: C18.2, U2.6 (COMP)
unnamed: R25.2, R26.1, U2.5 (FB)
unnamed: R23.1, U2.7 (RLIM)
unnamed: R76.1, U3.11
unnamed: R77.1, U3.14
unnamed: R75.1, U3.12
unnamed: C15.1, U3.10
unnamed: C47.1, R58.2, U9.8 (5VOUT)
unnamed: R60.1, U9.23 (BRA)
unnamed: R57.2, U9.27 (BRB)
unnamed: C48.1, U9.5 (CPI)
unnamed: C48.2, U9.4 (CPO)
unnamed: C45.1, U9.6 (VCP)
unnamed: R58.1, R59.2, U9.17 (VREF)
PGOOD: R22.2, U2.3 (EN), U3.16
PRODUCT_FLOWMETER: C3.1, D6.3 (COM), R7.2, U5.39
PRODUCT_TDS: D41.2 (A2), J28.1, R56.1, TP34.1
RS485_DERE: R64.2, U5.5, U10.2 (~RE), U10.3 (DE)
RS485_DI: R63.1, U5.25, U10.4 (DI)
RS485_RO: R65.1, U5.24, U10.1 (RO)
SCL: D16.2 (A2), J2.4, R17.1, TP10.1, TP12.1, U1.10 (SCL), U5.20
SDA: D17.2 (A2), J2.3, R18.1, TP11.1, TP13.1, U1.9 (SDA), U5.21
SERVO1: R11.2, U5.33
SERVO2: R12.1, U5.34
SOLENOID1: R13.2, R14.2, R15.1, U5.6
SOLENOID2: R32.2, R33.2, R34.1, U5.7
SOLENOID3: R35.2, R36.2, R37.1, U5.8
SOLENOID4: R38.2, R39.2, R40.1, U5.9
SOLENOID5: R69.2, R70.2, R71.1, U5.12
TMC2209_DIAG: U5.23, U9.11 (DIAG)
TMC2209_DIR: U5.11, U9.19 (DIR)
TMC2209_EN: R55.2, U5.19, U9.2 (~EN)
TMC2209_RX: R54.1, U5.17
TMC2209_STEP: U5.10, U9.16 (STEP)
TMC2209_TX: R54.2, U5.18, U9.14 (~PD/UART)
WATER_TEMPERATURE: R62.1, U5.32

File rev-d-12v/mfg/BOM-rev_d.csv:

Comment,Designator,Footprint,LCSC Part #
RT7272BGSP,U2,SOIC-8_L5.0-W4.0-P1.27-LS6.0-BL-EP2.0,C127866
22uF,"C19, C20",C_1206_3216Metric,C12891
10uF,"C11, C12, C13, C14, C22, C46, C49",C_1206_3216Metric,C13585
100nF,"C2, C5, C8, C10, C15, C16, C32, C34, C36, C41, C44, C45, C50, C51, C54, C60",C_0603_1608Metric,C14663
AO3401A,"Q9, Q10",SOT-23,C15127
1uF,"C1, C4, C6, C7, C25, C26, C27, C28, C29, C30, C31, C35, C58, C61, C62, C63",C_0603_1608Metric,C15849
Conn_01x04_MountingPin,J2,JST_SH_BM04B-SRSS-TB_1x04-1MP_P1.00mm_Vertical,C160390
2.2nF,"C3, C18, C24",C_0603_1608Metric,C1604
470pF / 50V,"C52, C53, C55, C56",C_0603_1608Metric,C1620
6.8uH,L2,L_Chilisin_BMRA00050530,C177249
TPS16630PWPR,U3,HTSSOP-20-1EP_4.4x6.5mm_P0.65mm_EP3.4x6.5mm_Mask2.96x2.96mm,C1849461
BZT52C10,D56,D_SOD-123,C19077408
SMBJ16CA,"D15, D19, D27, D30, D33, D48",D_SMB,C19077572
4.7uF,C47,C_0603_1608Metric,C19666
10uF,"C9, C59",C_0603_1608Metric,C19702
5x20mm,F1,Fuseholder_Cylinder-5x20mm_LittelFuse_646,C206887
AO3400A,"Q1, Q2, Q4, Q5, Q6, Q7",SOT-23,C20917
22nF / 50v,C48,C_0603_1608Metric,C21122
0R,R75,R_0603_1608Metric,C21189
1k,"R13, R32, R35, R38, R54, R69",R_0603_1608Metric,C21190
TMC2209-LA,U9,VQFN-28-1EP_5x5mm_P0.5mm_EP3.7x3.7mm_ThermalVias,C2150710
1.2K,"R5, R29",R_0603_1608Metric,C22765
100R,"R9, R11, R12, R62",R_0603_1608Metric,C22775
12k,R26,R_0603_1608Metric,C22790
RED,"D13, D21, D22, D25, D28, D31, D39, D46",LED_0603_1608Metric,C2286
220R,"R15, R19, R34, R37, R40, R71",R_0603_1608Metric,C22962
4.7K,"R7, R8, R31, R61, R73, R76",R_0603_1608Metric,C23162
5.1k,R51,R_0603_1608Metric,C23186
62k 1%,R25,R_0603_1608Metric,C23221
82k 1%,R23,R_0603_1608Metric,C23254
24k,"R22, R24, R72",R_0603_1608Metric,C23352
BAV99,"D4, D9, D35, D42",SOT-23,C2500
10k,"R1, R2, R4, R10, R14, R16, R20, R28, R33, R36, R39, R42, R56, R59, R63, R64, R65, R70, R78",R_0603_1608Metric,C25804
47k,R27,R_0603_1608Metric,C25819
MAX40200AUK,U4,SOT-23-5,C2649430
PESD3V3L1BA,"D3, D5, D7, D8, D11, D12, D16, D17, D23, D34, D41, D43",D_SOD-323,C2687129
100uF / 35v,C57,CP_Elec_6.3x7.7,C2836442
SMAJ5.0A,"D1, D2, D10",D_SMA,C2925443
SMF30CA,"D50, D51, D52, D53, D54, D55",D_SOD-123F,C2990493
PSM712,D44,SOT-23,C32677
0.11R 1%,"R57, R60",R_1206_3216Metric,C327071
220uF / 16v,"C21, C23",CP_Elec_6.3x7.7,C3342
ADS1115IDGSR,U1,TSSOP-10_3x3mm_P0.5mm,C37593
50ohm @ 100mhz,"FB2, FB3, FB4, FB5",L_0603_1608Metric,C394425
20k,"R55, R58, R66, R68, R77",R_0603_1608Metric,C4184
2.2k,"R6, R17, R18, R30, R74",R_0603_1608Metric,C4190
3.5MM,"J3, J7, J10, J12, J14, J16, J18, J25","PhoenixContact_MC_1,5_2-G-3.5_1x02_P3.50mm_Horizontal",C5188295
3.5MM,"J1, J4, J5, J6, J11, J22, J23, J28, J29","PhoenixContact_MC_1,5_3-G-3.5_1x03_P3.50mm_Horizontal",C5188296
3.5MM,J21,"PhoenixContact_MC_1,5_4-G-3.5_1x04_P3.50mm_Horizontal",C5188297
PSD12C,D45,D_SOD-323,C5199854
22uF,C33,C_0603_1608Metric,C59461
mSMD260,F2,Fuse_1812_4532Metric,C70129
100R 0.1%,"R3, R41",R_1206_3216Metric,C728670
BAT54S,"D6, D24",SOT-23,C7420333
1N4148W,"D18, D20",D_SOD-123,C81598
SS34,"D14, D26, D29, D32, D47, D49, D57",D_SMA,C8678
SP3485EN,U10,SOIC-8_3.9x4.9mm_P1.27mm,C8963
Buzzer,BZ1,MagneticBuzzer_QMB-09B-03,C96256
Female header 1x22 2.54mm 8.5mm,"U5A, U5B",PinSocket_1x22_P2.54mm_Vertical,C41376161

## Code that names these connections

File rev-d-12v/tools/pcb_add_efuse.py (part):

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  3. Output: U3's OUT pins 18-20 and C22 share a new +12V area with five vias to the inner +12V plane (In2). TP41 (bottom test pad)
     moves onto one of those vias.
  4. ILIM R76, MODE R75 (0R) and IMON R77 right of U3; dVdT C15 below it; exposed pad with 14 vias to GND.
  5. PGOOD: from U3 pin 16 through a via and the bottom layer to the existing track to the buck enable (U2 pin 3); R22 (24k pull-up)
     moves to the right of the resistor column and joins the same bottom-layer track.
  6. D49 (SS34, output Schottky) moves to the free space between Q7 and F1 with its own +12V area and vias; the "FUSE 5x20" label moves
     to the right of F1. C22 moves 1 mm to the right. D20-A's via moves 0.2 mm so that R74 fits.
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assert at(pad('U3', '1').GetPosition(), 140.4375, 64.275) and at(pad('U3', '20').GetPosition(), 146.1625, 64.275)

# left of U3: P_IN, UVLO, OVP, GND, dVdT
track(PFO, pcbnew.F_Cu, 0.25, (140.1, 67.525), (139.2, 67.525), (139.2, 65.45))                     # P_IN (pin 6) up to the PFET_OUT area
track(PFO, pcbnew.F_Cu, 0.3, (136.675, 66.25), (136.675, 65.4))                                      # R72 to the PFET_OUT area
track(PS + "EF_UVLO", pcbnew.F_Cu, 0.25, (140.1, 68.175), (138.325, 68.175))                          # pin 7 - R73
track(PS + "EF_UVLO", pcbnew.F_Cu, 0.25, (138.325, 66.25), (138.325, 67.85))                          # R72 - R73
track(PS + "EF_OVP", pcbnew.F_Cu, 0.2, (140.1, 68.825), (136.675, 68.825))                            # pin 8, between R73 and R74
track(PS + "EF_OVP", pcbnew.F_Cu, 0.25, (136.675, 67.85), (136.675, 69.65))                           # R73 - R74
track(GND, pcbnew.F_Cu, 0.3, (138.325, 69.65), (138.325, 69.475), (142.0, 69.475))                     # R74 and pin 9 to the exposed pad
track("Net-(U3-dVdT)", pcbnew.F_Cu, 0.25, (140.1, 70.125), (139.625, 70.6), (139.625, 71.55))          # pin 10 - C15
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FPS['TP41'].SetPosition(P(147.425, 64.45))
for x, y in ((152.25, 63.9), (152.25, 65.3)): via(GND, x, y, 0.45)                                    # C22's ground pad

# ---- 5. PGOOD: U3 pin 16 -> via -> bottom layer -> via at (135.2, 71.2) -> the existing track to U2; R22 joins on the bottom layer
FPS['R22'].SetPosition(P(151.72, 67.6)); FPS['R22'].SetOrientationDegrees(270)
assert pad('R22', '1').GetNetname() == P12 and at(pad('R22', '1').GetPosition(), 151.72, 66.775)
track(PG, pcbnew.F_Cu, 0.25, (146.5, 66.875), (146.95, 66.875), (147.45, 66.375)); via(PG, 147.45, 66.375, 0.45)
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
